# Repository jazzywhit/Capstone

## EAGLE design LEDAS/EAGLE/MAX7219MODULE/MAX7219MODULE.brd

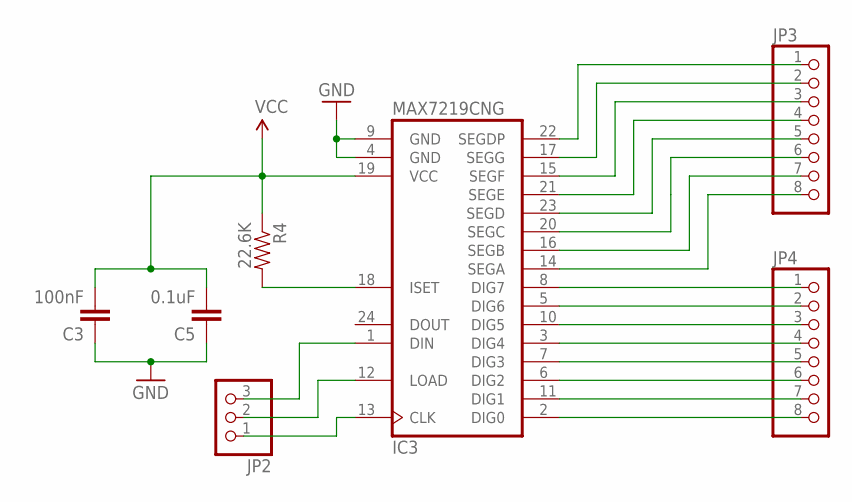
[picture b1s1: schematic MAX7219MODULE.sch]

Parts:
C3: 100nF; CAP-PTH-SMALL2
C5: 0.1uF; CAP-PTH-SMALL2
IC3: MAX7219CNG; DIL24-3
JP2: PINHD-1X3CB; 1X03-CLEANBIG
JP3, JP4: PINHD-1X8CLEANBIG; 1X08-CLEANBIG
R4: 22.6K; AXIAL-0.5

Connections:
GND: C3.1, C5.1, IC3.4 (GND), IC3.9 (GND)
unnamed: IC3.1 (DIN), JP2.3
unnamed: IC3.12 (LOAD), JP2.2
unnamed: IC3.13 (CLK), JP2.1
unnamed: IC3.22 (SEGDP), JP3.1
unnamed: IC3.17 (SEGG), JP3.2
unnamed: IC3.15 (SEGF), JP3.3
unnamed: IC3.21 (SEGE), JP3.4
unnamed: IC3.23 (SEGD), JP3.5
unnamed: IC3.20 (SEGC), JP3.6
unnamed: IC3.16 (SEGB), JP3.7
unnamed: IC3.14 (SEGA), JP3.8
unnamed: IC3.8 (DIG7), JP4.1
unnamed: IC3.5 (DIG6), JP4.2
unnamed: IC3.10 (DIG5), JP4.3
unnamed: IC3.3 (DIG4), JP4.4
unnamed: IC3.7 (DIG3), JP4.5
unnamed: IC3.6 (DIG2), JP4.6
unnamed: IC3.11 (DIG1), JP4.7
unnamed: IC3.2 (DIG0), JP4.8
unnamed: IC3.18 (ISET), R4.P$2 (2)
VCC: C3.2, C5.2, IC3.19 (VCC), R4.P$1 (1)

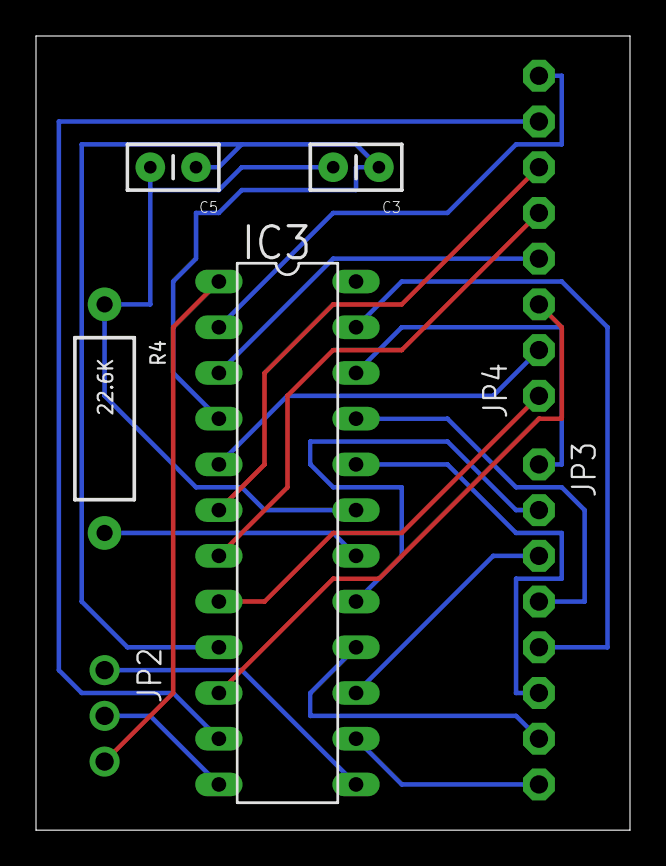
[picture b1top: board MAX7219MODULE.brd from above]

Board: 2 copper layers, 33.0 x 44.1 mm, 7 parts (0 on the bottom side), 22 nets.

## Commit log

2012-09-11 Create the Ocelot project in Eclipse.
    Went with Ice Cream Sandwich. Does not run as an application yet.
    Initial commit to get the files up and synched with Matt.
2012-09-12 A few functions seem to not work out of the gate. Maybe it is just eclipse being weird, and maybe I should have used a branch, but I think this needs to be resolved in master before further work is d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
2012-09-13 Syncfiles
2012-09-13 Set ignore on .DS_Store
    Should be ignored...
2012-10-10 Successful import of project in eclipse. Modified .gitignore to not hold onto extra, non-code, files.
2012-10-10 First working app. - Configured the Manifest Intent to show the app
    - Added some basic soundboard abilities
    - Added sounds and pictures
    /
2012-10-10 Milestone 1. - Uploaded the images and sounds (last commit was incorrect) - Uploaded classes needed for the soundboard.
2012-10-11 Realized that not all the necessary files were uploaded. - removed files from .gitignore until I can be sure of what we need for easy deployment.
2012-10-11 Added Menu Actions. - removed .metadata with .gitignore - Added bin/ - Added some new images for buttons - Updates for the new menu actions.
2012-10-14 Added an elephant so we can have 4 objects to arrange in a grid - Next step will be to arrange in a grid - Make size of objects uniform - Add a sequence bar - Allow for drag and drop into the sequenc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
2012-10-14 Implemented GridView with 2 columns -Need to get sound working -Need to override the method for onclick()
2012-10-15 Deploying on OS X to figure out what files are unnecessary. - removed *.class files, as they are created by eclipse - removed *.cache files - removed gen/ files - updated .gitignore.
2012-10-15 GridView now workign with sound. - SoundBoardItem is now contains the name of the object and the sound. - Single click shows the name of the animal. - Long click plays a sound!.
2012-10-16 Removed more files that should not be on the repository. - .apk and related files. - temporary images that were beign creatd.
2012-10-16 Changed behavior of clicks. - short -> description - long -> sound
2012-10-16 Implement Main Menu
    Main Menu does not work. Creating a branch to accomplish the task.
2012-10-16 Drag and Drop. - Put in initial drag and drop - The same OnTouchListener will also play sounds. - Currently losing the object on drag. Need to implement an OnDragListener or some other method.
2012-10-18 Added another object that we can possibly drag to. - Next step is to allow dragging back and forth. - Ensure that both grids allow playback of sound.
2012-10-18 New Soundboard Package. Major changes to layout. - Changed the main layout of the Soundboard to ensure a sequence bar. - Started adding the sequence bar classes. - STATUS: Not functional. - TODO: Imp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
2012-10-22 Sequence Bar Milestone. - Added Sequence Bar - Correctly scrolls side->side - Issues with spacing.
2012-10-22 Incremental changes to Sequence Bar. - Modified a number of padding variables but still not finding a solution.
2012-10-23 Added Gallery view for the Sequence Bar
2012-10-23 Added Playback of the sequence items and set size correctly.
2012-10-27 Attempting to get the music playing sequentially and synchronizing properly.
2012-10-30 Sequence Bar is playing sounds in correct order. - Implemented OnCompletionListener properly - Added text back in for all objects.
2012-10-30 Code cleanup after SequenceBar Milestone.
2012-10-30 Working on Drag and Drop - Commit before bed - Listener is working properly - Need to craft a way to transfer the SoundBoardItem properly.
2012-10-30 Work on the Drag and Drop today before Capstone meeting.
2012-11-27 Drag and Drop working. - Moved all data out of the adapters and into the activity. - Updating the listeners to work from the Activity instead of the adapter. - Renamed Default -> SoundBoardActivity a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
2012-11-27 Sequence Progression works.
2012-11-27 Added a border to the Sequence View
2012-11-28 Adding initial support for the database. Adding Text and Image view to the Grid.
2012-11-29 Some progress on the images - Put a box around them for easier viewing - Text and Image are showing - Text is not in the right place
2012-11-29 Adding new icon layout.
2012-11-29 Some small updates. Still unable to get it to behave properly.
2012-12-04 Added text to speech, updated methods for support. - Allow for SoundBoardItem to not have image or sound. If it has sound it plays the sound. If it has image it displays image. If it is missing the s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
2012-12-04 Fixed the issue with Drag and Drop and non-empty sequence list. - Put the drag listener on the scroll view.
2012-12-09 Adding context and dialog boxes for new game, new item. - popup box is not shutting down when the button is pressed. - Need to add items to the popup box.
2012-12-09 LED A Sketch
    Working on two of our 7x7 boards. Will be adding 2 more and
    transitioning them to perf board.
2012-12-10 Added new class for custom Alert Dialog. - Might be best to add a new activity for the new item
2012-12-11 New Item Dialog is working now, collects data. - Changed from 1.5 -> 1.6 - Removed some extra commented code - Added strings, updated the popup.xml for the new item dialog
2012-12-11 Added Delete Mode menu item and basic infrastructure.
2012-12-11 Four Matrix Code
    Updated to another project to include all four matrix modules.
    Used for testing of LED driver board.
2012-12-11 New Item dialog changes - Added sound recording functionality - Updated the images on the record and playback buttons - Correctly plays media back
2012-12-16 Restructuring File System
    Organizing files and folders to easy access to repository files.
2012-12-16 Skeleton Code for LEDAS
    added sketleton code for LEDAS project
2012-12-16 Prototype code for testing LEDAS Module
    Test code for
    -Debounce
    -Matrix Update
    -Image creation continuity
2012-12-18 Adding Synthesize to file.
2012-12-18 Got the LED and controller working
    Also added Arduino software
2012-12-18 Improvements for blinking and bounds detection
2012-12-19 Got Synthesis working for TTS and attempting to streamline. - Issues still with changes to the listeners (GridView). - Sort is working but is not displaying properly. (Likely an issue with the listen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
2012-12-19 Added new border elements and new folder for drawable objects.
2012-12-19 Added Image Selector Intent.
2012-12-21 Added a lot of new look and feel onto the platform.
2012-12-21 Small fixes for JellyBean - Grid was not updating at the right times.
2012-12-21 Reorganized the new item menu. Got image adding working properly. All that is left is saving to datbase and fixing the gridview repetition.
2012-12-21 Implementing Serializable - Fixed Menus - Added support contact info.
2012-12-21 Small GUI changes - Renamed menus - Allowed for individual deletion from the sequence bar - Made New Game easier and fixed bug.
2012-12-21 Added a Schematic and removed the Database Connector.
2012-12-21 Added the printed code and schematics
2012-12-21 Some final changes before submission to the client. There are still a number of issues that need to be solved. - Higher Contrast Buttons - Organizign the Sequence Bar with drag-drop - Take off the lo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
2012-12-21 Combined all the code files into one.

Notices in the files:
parts and their libraries:
SparkFun: Licensing: CC v3.0 Share-Alike You are welcome to use this library for commercial purposes.
